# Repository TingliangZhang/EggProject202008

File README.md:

# EggProject202008
# 整体选型 

主控： 

ARDUINO NANO 33 BLE SENSE 

[https://store.arduino.cc/usa/nano-33-ble-sense-with-headers](https://store.arduino.cc/usa/nano-33-ble-sense-with-headers)

灯环： 

NeoPixel Jewel - 7 x 5050 RGBW LED w/ Integrated Drivers - Warm White - ~3000K 

[https://www.adafruit.com/product/2858](https://www.adafruit.com/product/2858)

- [ ] 5V锂电+充电宝备用（7.4V锂电+降压？/ 21V耐压NANO的Vin直接接杜邦线？灯环功率会不会太大）——短USB备用 

稍稍小一点的充电宝备用？ 

[https://item.taobao.com/item.htm?spm=a1z0d.7625083.1998302264.5.5c5f4e692QkVvK&id=613935874629](https://item.taobao.com/item.htm?spm=a1z0d.7625083.1998302264.5.5c5f4e692QkVvK&id=613935874629)

最终购买充电宝： 

飞利浦10000mAh充电宝 

[https://item.jd.com/100014325484.html](https://item.jd.com/100014325484.html)

86x86x16.6mm 

得考虑Micro USB线 

- [ ] 电烙铁/焊锡丝（管式的好，锡丝枪）jd购买 
- [ ] 导线/杜邦线 

调研NANO的麦克风能输出吗？有例程吗 

外形得定一下，用半透明透光白色塑料3D打印，还得看看里面怎么塞这些元件 

线性震动马达能不能买到手感如何未知： 

买不到线性马达就只能买震动马达电机模块，比如 

[https://detail.tmall.com/item.htm?spm=a230r.1.14.16.41e16394zkbMDu&id=601459320149&ns=1&abbucket=10](https://detail.tmall.com/item.htm?spm=a230r.1.14.16.41e16394zkbMDu&id=601459320149&ns=1&abbucket=10)

能不能驱动未知，没用过 

最终选用震动马达 

[https://detail.tmall.com/item.htm?id=577879484815&spm=a1z09.2.0.0.413f2e8dfnTjBj&_u=k2q6uuhe675a](https://detail.tmall.com/item.htm?id=577879484815&spm=a1z09.2.0.0.413f2e8dfnTjBj&_u=k2q6uuhe675a)

发光触摸开关 

[https://detail.tmall.com/item.htm?id=17966563330&spm=a1z09.2.0.0.413f2e8dfnTjBj&_u=k2q6uuheb10c](https://detail.tmall.com/item.htm?id=17966563330&spm=a1z09.2.0.0.413f2e8dfnTjBj&_u=k2q6uuheb10c)

电容式触摸开关 

[https://detail.tmall.com/item.htm?id=520842104957&spm=a1z09.2.0.0.413f2e8dfnTjBj&_u=k2q6uuhe56ca](https://detail.tmall.com/item.htm?id=520842104957&spm=a1z09.2.0.0.413f2e8dfnTjBj&_u=k2q6uuhe56ca)

# Arduino NANO 33 BLE Sense 

Getting started with the Arduino NANO 33 BLE Sense 

[https://www.arduino.cc/en/Guide/NANO33BLESense](https://www.arduino.cc/en/Guide/NANO33BLESense)

5V on that pin is available only when two conditions are met: you make a solder bridge on the two pads marked as VUSB and you power the NANO 33 BLE Sense through the USB port. 

所以只能从USB驱动它了，注意焊上VBUS 

用得到的模块 

I2C 

BLE 

做机器学习？ 

[https://www.arduino.cc/en/AI/HomePage](https://www.arduino.cc/en/AI/HomePage)

TinyML: Wake Word Detection 

An embedded application for wake word detection which is implemented on Arduino Nano 33 BLE Sense 

machine learning 

[https://create.arduino.cc/projecthub/ariceh/tinyml-wake-word-detection-1628c0?ref=part&ref_id=107215&offset=17](https://create.arduino.cc/projecthub/ariceh/tinyml-wake-word-detection-1628c0?ref=part&ref_id=107215&offset=17)

# MCU参数和Datasheet 

| Microcontroller             | nRF52840 [(datasheet)](https://content.arduino.cc/assets/Nano_BLE_MCU-nRF52840_PS_v1.1.pdf) |
| :-------------------------- | :----------------------------------------------------------- |
| Operating Voltage           | 3.3V                                                         |
| Input Voltage (limit)       | 21V                                                          |
| DC Current per I/O Pin      | 15 mA                                                        |
| Clock Speed                 | 64MHz                                                        |
| CPU Flash Memory            | 1MB (nRF52840)                                               |
| SRAM                        | 256KB (nRF52840)                                             |
| EEPROM                      | none                                                         |
| Digital Input / Output Pins | 14                                                           |
| PWM Pins                    | all digital pins                                             |
| UART                        | 1                                                            |
| SPI                         | 1                                                            |
| I2C                         | 1                                                            |
| Analog Input Pins           | 8 (ADC 12 bit 200 ksamples)                                  |
| Analog Output Pins          | Only through PWM (no DAC)                                    |
| External Interrupts         | all digital pins                                             |
| LED_BUILTIN                 | 13                                                           |
| USB                         | Native in the nRF52840 Processor                             |
| IMU                         | LSM9DS1 ( [datasheet](https://content.arduino.cc/assets/Nano_BLE_Sense_lsm9ds1.pdf)) |
| Microphone                  | MP34DT05 ( [datasheet](https://content.arduino.cc/assets/Nano_BLE_Sense_mp34dt05-a.pdf)) |
| Gesture, light, proximity   | APDS9960 ( [datasheet](https://content.arduino.cc/assets/Nano_BLE_Sense_av02-4191en_ds_apds-9960.pdf)) |
| Barometric pressure         | LPS22HB ( [datasheet](https://content.arduino.cc/assets/Nano_BLE_Sense_lps22hb.pdf)) |
| Temperature, humidity       | HTS221 ( [datasheet](https://content.arduino.cc/assets/Nano_BLE_Sense_HTS221.pdf)) |
| Length                      | 45 mm                                                        |
| Width                       | 18 mm                                                        |
| Weight                      | 5 gr (with headers)                                          |

# 尺寸要求 

主板：ARDUINO NANO 33 BLE SENSE 

[https://store.arduino.cc/usa/nano-33-ble-sense-with-headers](https://store.arduino.cc/usa/nano-33-ble-sense-with-headers)

45x18mm 片状 可能会有排针 

充电宝 

应该是外置，如果蛋特别大就内置 

最终购买充电宝：飞利浦10000mAh充电宝 

[https://item.jd.com/100014325484.html](https://item.jd.com/100014325484.html)

86x86x16.6mm 

得考虑Micro USB线 

RGBW LED 圆片 

Diameter: 22.95mm / 0.9" 

# 代码编写 

项目可以参考ProjectHub 

[https://create.arduino.cc/projecthub/products/nano-33-ble-sense](https://create.arduino.cc/projecthub/products/nano-33-ble-sense)

里面的项目 

## Blink测试： 

Getting started with the Arduino NANO 33 BLE Sense 

[https://www.arduino.cc/en/Guide/NANO33BLESense](https://www.arduino.cc/en/Guide/NANO33BLESense)

需要安开发板 Arduino nRF528x mbed Core 

## Neopixel测试： 

NeoPixel Jewel - 7 x 5050 RGBW LED w/ Integrated Drivers - Warm White - ~3000K 

[https://www.adafruit.com/product/2858](https://www.adafruit.com/product/2858)

注意使用RGBWstrandtest例程，并改 

// How many NeoPixels are attached to the Arduino? 

#define LED_COUNT  7 

需要安装库 Adafruit NeoPixel by Adafruit 

Arduino Library Installation 

[https://learn.adafruit.com/adafruit-neopixel-uberguide/arduino-library-installation](https://learn.adafruit.com/adafruit-neopixel-uberguide/arduino-library-installation)

## 线性马达测试 

直接接上，用Blink的代码试试 

## 手势交互测试 

**Gesture sensor on the Arduino NANO 33 BLE Sense** 

The Gesture sensor is a [APDS9960](https://docs.broadcom.com/docs/AV02-4191EN), it senses gesture, color, ambience illumination and proximity . This chip, made by Broadcom is supported by our library [ArduinoAPDS9960](https://www.arduino.cc/en/Reference/ArduinoAPDS9960). The library contains, as usual, the example sketches to use the sensor for gestures, color and proximity. 

[https://www.arduino.cc/en/Reference/ArduinoAPDS9960](https://www.arduino.cc/en/Reference/ArduinoAPDS9960)

To use this library 

`#include <Arduino_APDS9960.h>`  

运行FullExample先试试 

## 麦克风测试 

**Digital microphone on the Arduino NANO 33 BLE Sense** 

The digital microphone is a [MP34DT05](https://www.st.com/resource/en/datasheet/mp34dt05-a.pdf), This chip, made by ST Microelectronics, is an ultra-compact, low-power, omnidirectional, digital MEMS microphone built with a capacitive sensing element and an IC interface; it produces an output coded in [PDM](https://en.wikipedia.org/wiki/Pulse-density_modulation). The PDM format is supported by our library [PDM](https://www.arduino.cc/en/Reference/PDM)that can be used also with our [ArduinoSound](https://www.arduino.cc/en/Reference/ArduinoSound). The PDM library contains, as usual, the example sketches to use the sensor. 

[https://www.arduino.cc/en/Reference/ArduinoSound](https://www.arduino.cc/en/Reference/ArduinoSound)

To use this library 

`#include <AudioSound.h>`  

但是显示Incompatible，不知道能不能用哦 

试试例程AmplitudeSerialPlotter 

可以用开发版自带例程PDM SerialPlotter 

## //麦克风截取关键词测试 

## //录音幅频显示测试 

## 离线机器学习语音转文字测试 

机器学习： [https://www.arduino.cc/en/AI/HomePage](https://www.arduino.cc/en/AI/HomePage)

主要参考： 

[Voice recognition Arduino_TensorFlowLite](https://blog.arduino.cc/2019/10/15/get-started-with-machine-learning-on-arduino/)

[https://blog.arduino.cc/2019/10/15/get-started-with-machine-learning-on-arduino/](https://blog.arduino.cc/2019/10/15/get-started-with-machine-learning-on-arduino/)

search for and install the Arduino_LSM9DS1 library 

## IMU晃动检测功能测试 

[Arduino_LSM9DS1](https://github.com/arduino-libraries/Arduino_LSM9DS1)

Allows you to read the accelerometer, magnetometer and gyroscope values from the LSM9DS1 IMU on your Arduino Nano 33 BLE Sense. 

## 蓝牙功能测试 

使用 

To use this library 

`#include <ArduinoBLE.h>`  

[https://www.arduino.cc/en/Reference/ArduinoBLE](https://www.arduino.cc/en/Reference/ArduinoBLE)

## 录音保存测试 

录音或许可以存在SD卡里面，SD卡通过USB连接到USB host上，但是如何实现待议 

**Serial ports on the Arduino NANO 33 BLE Sense** 

The USB connector of the board is directly connected to the native USB of the NINA B306 module. This routing enables you to use the Arduino NANO 33 BLE Sense as a client USB peripheral (acting as a mouse or a keyboard connected to the computer) or as a USB host device so that devices like a mouse, keyboard, or an Android phone can be connected to the Arduino NANO 33 BLE. This port can also be used as a virtual serial port using the **Serial** object in the Arduino programming language. The RX0 and TX1 pins are a second serial port available as **Serial1** . 

# 亮点 

* 使用RGBW全彩LED，白光偏暖色调 
* 使用TensorFlow Lite Micro在Arduino上面运行机器学习程序，进行离线的NLP识别 
* 通过BLE和手机连接，连接稳定，带宽甚至可以直接传输录音源文件 
* NFC兼具NFC tag识别和小功率无线充电功能 
* 使用APDS9960环境光传感器进行手势交互，交互高效自然且准确率高 
* 使用线性马达震动，手感好 
* IMU+机器学习进行晃动操作检测 
* 内置温湿度/大气压传感器，可扩展舒适度提醒功能 
* RGBW光谱传感器，感受环境光颜色 
* 造价低，量产单台造价低于100人民币 

# 成本 

| 序号 | 名称                                                         | 目前成本 | 备注         | 极限造价 |
| :--- | :----------------------------------------------------------- | :------- | :----------- | :------- |
| 1    | ARDUINO NANO 33 BLE SENSE                                    | $33.40   | 开源可自制   | ¥50      |
| 2    | NeoPixel Jewel - 7 x 5050 RGBW LED                           | $6.95    | 开源可自制   | ¥5       |
| 3    | [震动马达电机模块](https://detail.tmall.com/item.htm?id=601459320149&ad_id=&am_id=&cm_id=140105335569ed55e27b&pm_id=&abbucket=10) | ¥5       |              | ¥3       |
| 4    | 充电宝                                                       | ¥112     | 锂电替代     | ¥10      |
| 5    | 连接线                                                       | ¥10      | 跳线/PCB     | ¥1       |
| 6    | 触摸开关                                                     | ¥10      | 自己设计     | ¥2       |
| 7    | NFC线圈                                                      | ---      | NANO可直接接 | ¥5       |
| 8    | 3D打印                                                       |          | 批量制作     | ¥5       |

# 未来发展 

真正要认真做语音交互的话要用强大一点的板 

比如： 

Respeaker Core AI智能语音识别开发板IOT物联网方案RK3229芯片 

[http://wiki.seeedstudio.com/cn/ReSpeaker_Core_v2.0/](http://wiki.seeedstudio.com/cn/ReSpeaker_Core_v2.0/)

[https://item.taobao.com/item.htm?spm=a1z10.5-c-s.w4002-22845078888.10.616d5d19iRnqVx&id=566241590290](https://item.taobao.com/item.htm?spm=a1z10.5-c-s.w4002-22845078888.10.616d5d19iRnqVx&id=566241590290)

Arduino CLI is an all-in-one solution that provides builder, boards/library manager, uploader, discovery and many other tools needed to use any Arduino compatible board and platforms. 

[https://github.com/arduino/arduino-cli](https://github.com/arduino/arduino-cli)

[https://arduino.github.io/arduino-cli/latest/](https://arduino.github.io/arduino-cli/latest/)

[Installing Librar](https://learn.adafruit.com/adafruit-all-about-arduino-libraries-install-use/how-to-install-a-library)[ies](https://learn.adafruit.com/adafruit-all-about-arduino-libraries-install-use/how-to-install-a-library)[ Manuall](https://learn.adafruit.com/adafruit-all-about-arduino-libraries-install-use/how-to-install-a-library)[y](https://learn.adafruit.com/adafruit-all-about-arduino-libraries-install-use/how-to-install-a-library)[Ins](https://learn.adafruit.com/adafruit-all-about-arduino-libraries-install-use/installing-a-library)[ta](https://learn.adafruit.com/adafruit-all-about-arduino-libraries-install-use/installing-a-library)[ll](https://learn.adafruit.com/adafruit-all-about-arduino-libraries-install-use/installing-a-library)[in](https://learn.adafruit.com/adafruit-all-about-arduino-libraries-install-use/installing-a-library)[g a L](https://learn.adafruit.com/adafruit-all-about-arduino-libraries-install-use/installing-a-library)[ibrar](https://learn.adafruit.com/adafruit-all-about-arduino-libraries-install-use/installing-a-library)[y on W](https://learn.adafruit.com/adafruit-all-about-arduino-libraries-install-use/installing-a-library)[i](https://learn.adafruit.com/adafruit-all-about-arduino-libraries-install-use/installing-a-library)[ndow](https://learn.adafruit.com/adafruit-all-about-arduino-libraries-install-use/installing-a-library)[s](https://learn.adafruit.com/adafruit-all-about-arduino-libraries-install-use/installing-a-library)

[I](https://learn.adafruit.com/adafruit-all-about-arduino-libraries-install-use/installing-a-library-on-mac-osx)[nstallin](https://learn.adafruit.com/adafruit-all-about-arduino-libraries-install-use/installing-a-library-on-mac-osx)[g a Library on Mac OSX](https://learn.adafruit.com/adafruit-all-about-arduino-libraries-install-use/installing-a-library-on-mac-osx)

[In](https://learn.adafruit.com/adafruit-all-about-arduino-libraries-install-use/installing-a-library-on-linux)[stalling](https://learn.adafruit.com/adafruit-all-about-arduino-libraries-install-use/installing-a-library-on-linux)[ ](https://learn.adafruit.com/adafruit-all-about-arduino-libraries-install-use/installing-a-library-on-linux)[a](https://learn.adafruit.com/adafruit-all-about-arduino-libraries-install-use/installing-a-library-on-linux)[ L](https://learn.adafruit.com/adafruit-all-about-arduino-libraries-install-use/installing-a-library-on-linux)[ibrary](https://learn.adafruit.com/adafruit-all-about-arduino-libraries-install-use/installing-a-library-on-linux)[ ](https://learn.adafruit.com/adafruit-all-about-arduino-libraries-install-use/installing-a-library-on-linux)[on](https://learn.adafruit.com/adafruit-all-about-arduino-libraries-install-use/installing-a-library-on-linux)[ Linu](https://learn.adafruit.com/adafruit-all-about-arduino-libraries-install-use/installing-a-library-on-linux)[x](https://learn.adafruit.com/adafruit-all-about-arduino-libraries-install-use/installing-a-library-on-linux)

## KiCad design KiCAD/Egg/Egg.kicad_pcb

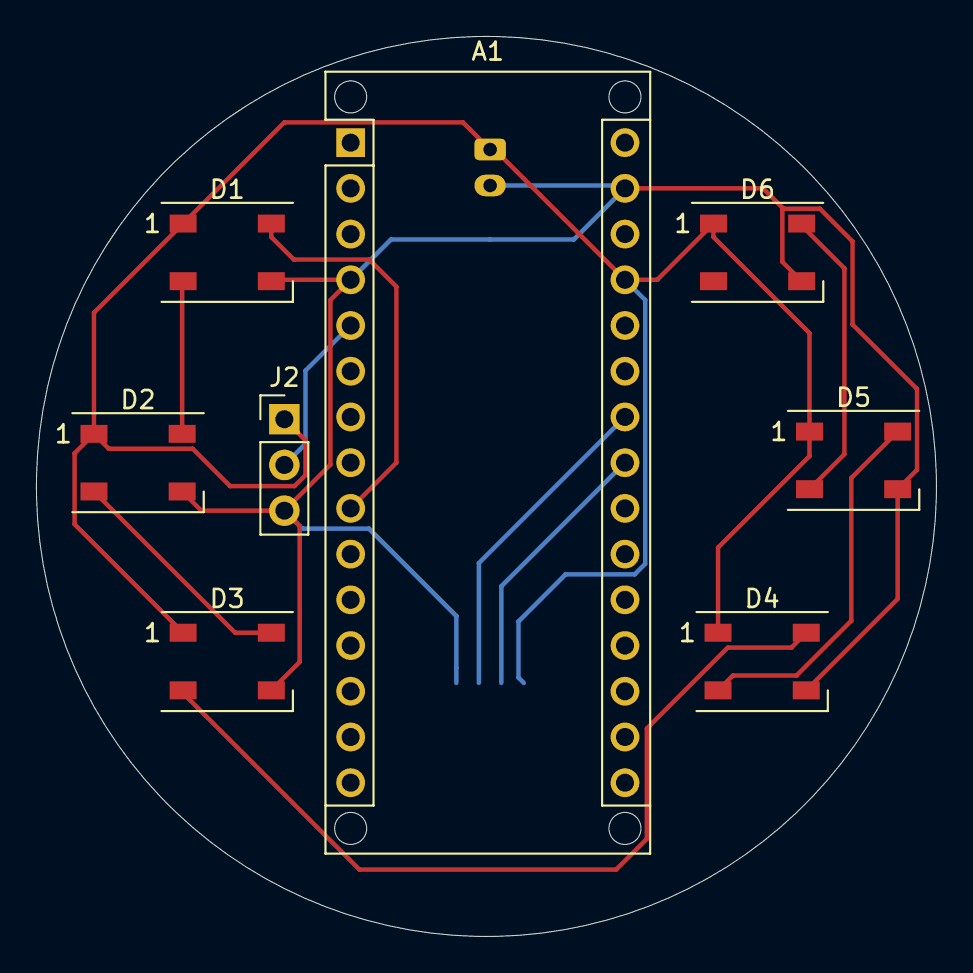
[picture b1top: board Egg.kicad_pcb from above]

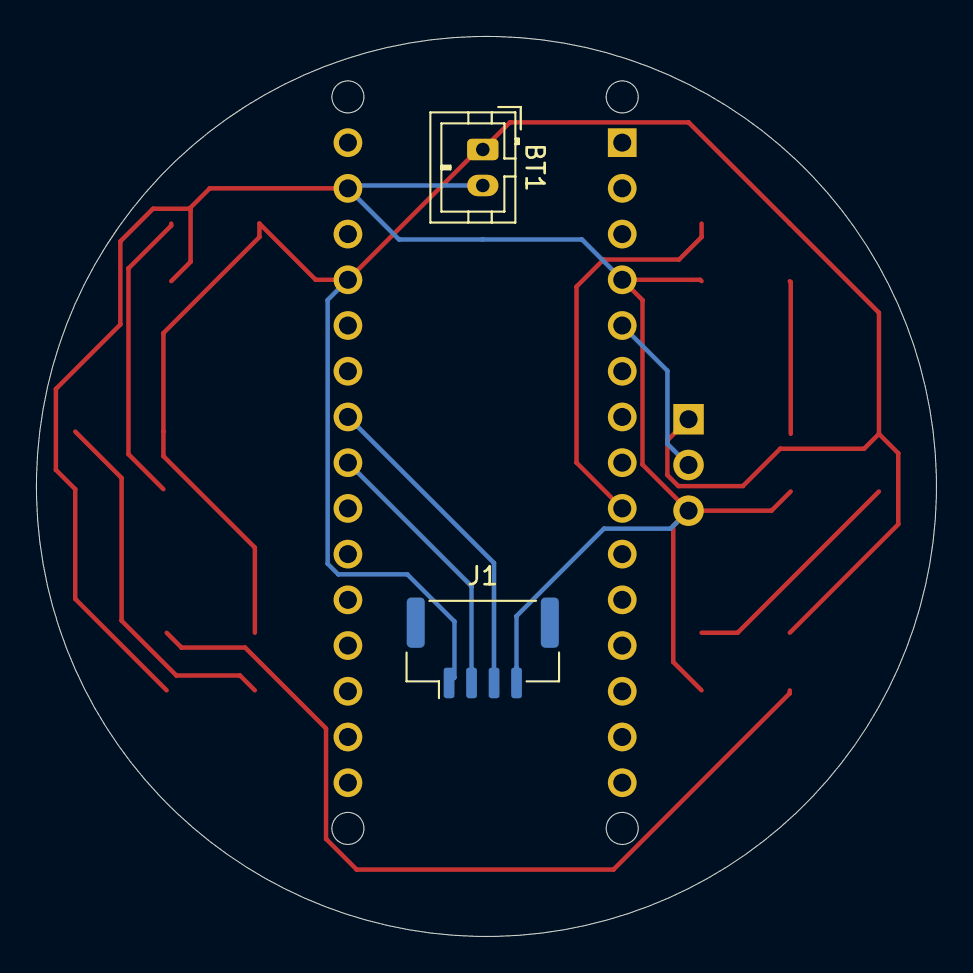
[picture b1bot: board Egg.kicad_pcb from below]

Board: 2 copper layers, 50.0 x 50.0 mm, 10 parts (2 on the bottom side), 11 nets.

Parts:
A1: Arduino_Nano_v2.x; Arduino_Nano_WithMountingHoles
BT1: Battery_Cell; JST_PH_B2B-PH-K_1x02_P2.00mm_Vertical
D1, D2, D3, D4, D5, D6: WS2812B; LED_WS2812B_PLCC4_5.0x5.0mm_P3.2mm
J1: Conn_01x04_NFC; JST_GH_BM04B-GHS-TBT_1x04-1MP_P1.25mm_Vertical
J2: Conn_01x03_Female_VibrationMotor; PinHeader_1x03_P2.54mm_Vertical

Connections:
+5V: A1.27, BT1.1, D1.1, D2.1, D3.1, D4.1, D5.1, D6.1, J1.1, J2.1
/RGBW: A1.9, D1.4
/SCL: A1.24, J1.3
/SDA: A1.23, J1.2
/VibrationMotor: A1.5, J2.2
GND: A1.4, A1.29, BT1.2, D1.3, D2.3, D3.3, D4.3, D5.3, D6.3, J1.4, J2.3
unnamed: D1.2, D2.4
unnamed: D2.2, D3.4
unnamed: D3.2, D4.4
unnamed: D4.2, D5.4
unnamed: D5.2, D6.4

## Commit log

2020-08-19 Gesture
2020-08-20 speech recognition
2020-08-20 ignore
2020-08-22 20200822比赛
2020-08-27 Kicad
2020-09-15 pdfs
2020-09-15 INI BOARD
2020-09-15 finish PCB
2020-09-16 NFC ini
2020-09-16 NFC PCB begin
2020-09-16 NFC coil
